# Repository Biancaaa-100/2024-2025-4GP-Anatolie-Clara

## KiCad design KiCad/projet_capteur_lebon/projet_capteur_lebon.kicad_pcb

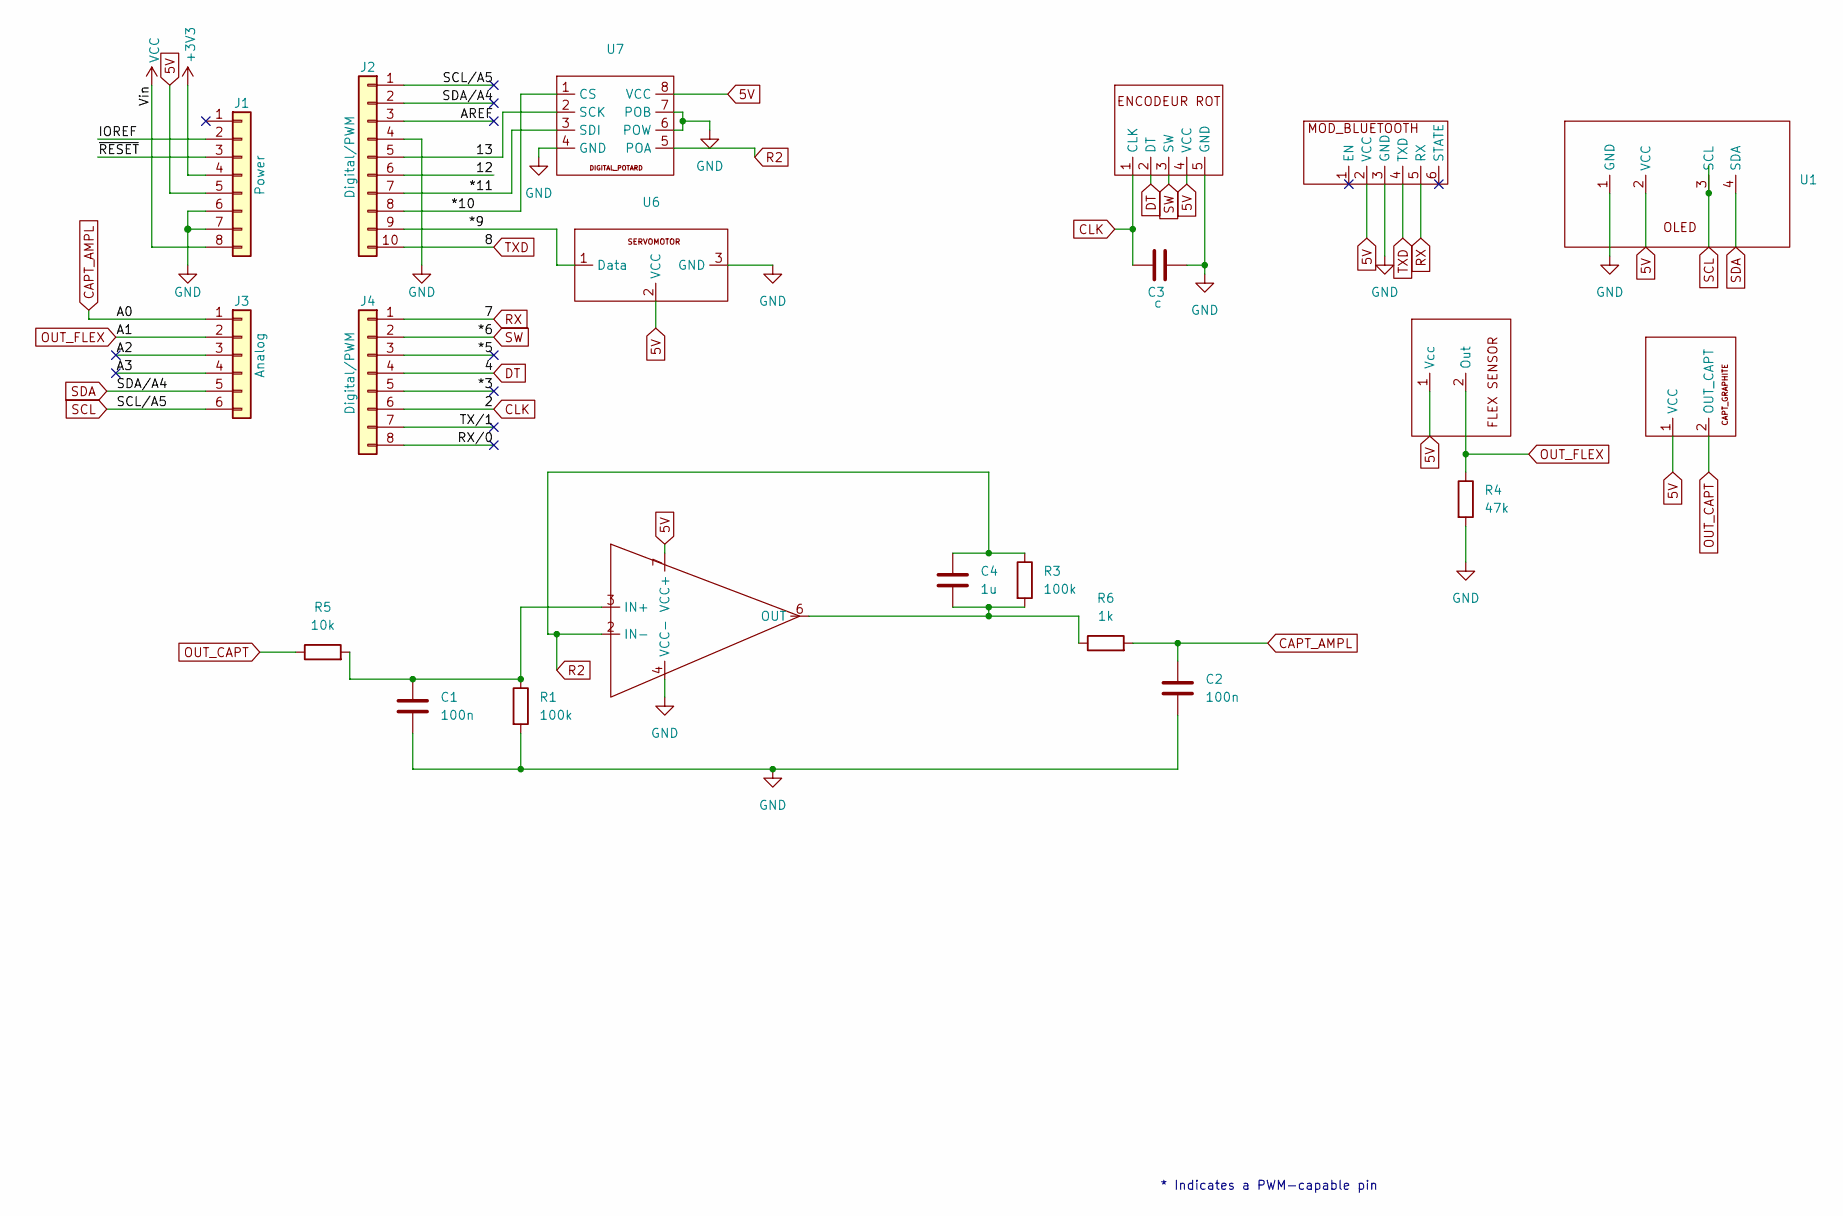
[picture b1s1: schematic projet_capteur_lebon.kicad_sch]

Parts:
C1, C2: 100n; C_Disc_D6.0mm_W2.5mm_P5.00mm
C3: c; C_Disc_D6.0mm_W2.5mm_P5.00mm
C4: 1u; C_Disc_D6.0mm_W2.5mm_P5.00mm
J1: Power; PinSocket_1x08_P2.54mm_Vertical
J2: Digital/PWM; PinSocket_1x10_P2.54mm_Vertical
J3: Analog; PinSocket_1x06_P2.54mm_Vertical
J4: Digital/PWM; PinSocket_1x08_P2.54mm_Vertical
R1, R3: 100k; R_Axial_DIN0207_L6.3mm_D2.5mm_P5.08mm_Vertical
R4: 47k; R_Axial_DIN0207_L6.3mm_D2.5mm_P5.08mm_Vertical
R5: 10k; R_Axial_DIN0207_L6.3mm_D2.5mm_P5.08mm_Vertical
R6: 1k; R_Axial_DIN0207_L6.3mm_D2.5mm_P5.08mm_Vertical
U1: SIP-4
U2: ENCODEUR ROT
U4, U7: DIP-8_296
U5: SIP-2
U6: SIP-3
U8: CAPTEUR_GRAPHITE
U9: BLUETOOTH

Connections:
5V: J1.5, U1.2 (VCC), U2.4 (VCC), U4.7 (VCC+), U5.1 (Vcc), U6.2 (VCC), U7.8 (VCC), U8.1 (VCC), U9.2 (VCC)
+3V3: J1.4
/12: J2.6
/13: J2.5, U7.2 (SCK)
/*3: J4.5
/*5: J4.3
/*9: J2.9, U6.1 (Data)
/*10: J2.8, U7.1 (CS)
/*11: J2.7, U7.3 (SDI)
/A2: J3.3
/A3: J3.4
/AREF: J2.3
/IOREF: J1.2
/RX/0: J4.8
/TX/1: J4.7
/~RESET: J1.3
CAPT_AMPL: C2.1, J3.1, R6.2
CLK: C3.1, J4.6, U2.1 (CLK)
DT: J4.4, U2.2 (DT)
GND: C1.2, C2.2, C3.2, J1.6, J1.7, J2.4, R1.2, R4.2, U1.1 (GND), U2.5 (GND), U4.4 (VCC-), U6.3 (GND), U7.4 (GND), U7.6 (POW), U7.7 (POB), U9.3 (GND)
unnamed: C1.1, R1.1, R5.2, U4.3 (IN+)
unnamed: C4.2, R3.2, R6.1, U4.6 (OUT)
OUT_CAPT: R5.1, U8.2 (OUT_CAPT)
OUT_FLEX: J3.2, R4.1, U5.2 (Out)
R2: C4.1, R3.1, U4.2 (IN-), U7.5 (POA)
RX: J4.1, U9.5 (RX)
SCL: J2.1, J3.6, U1.3 (SCL)
SDA: J2.2, J3.5, U1.4 (SDA)
SW: J4.2, U2.3 (SW)
TXD: J2.10, U9.4 (TXD)
VCC: J1.8

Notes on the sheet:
* Indicates a PWM-capable pin

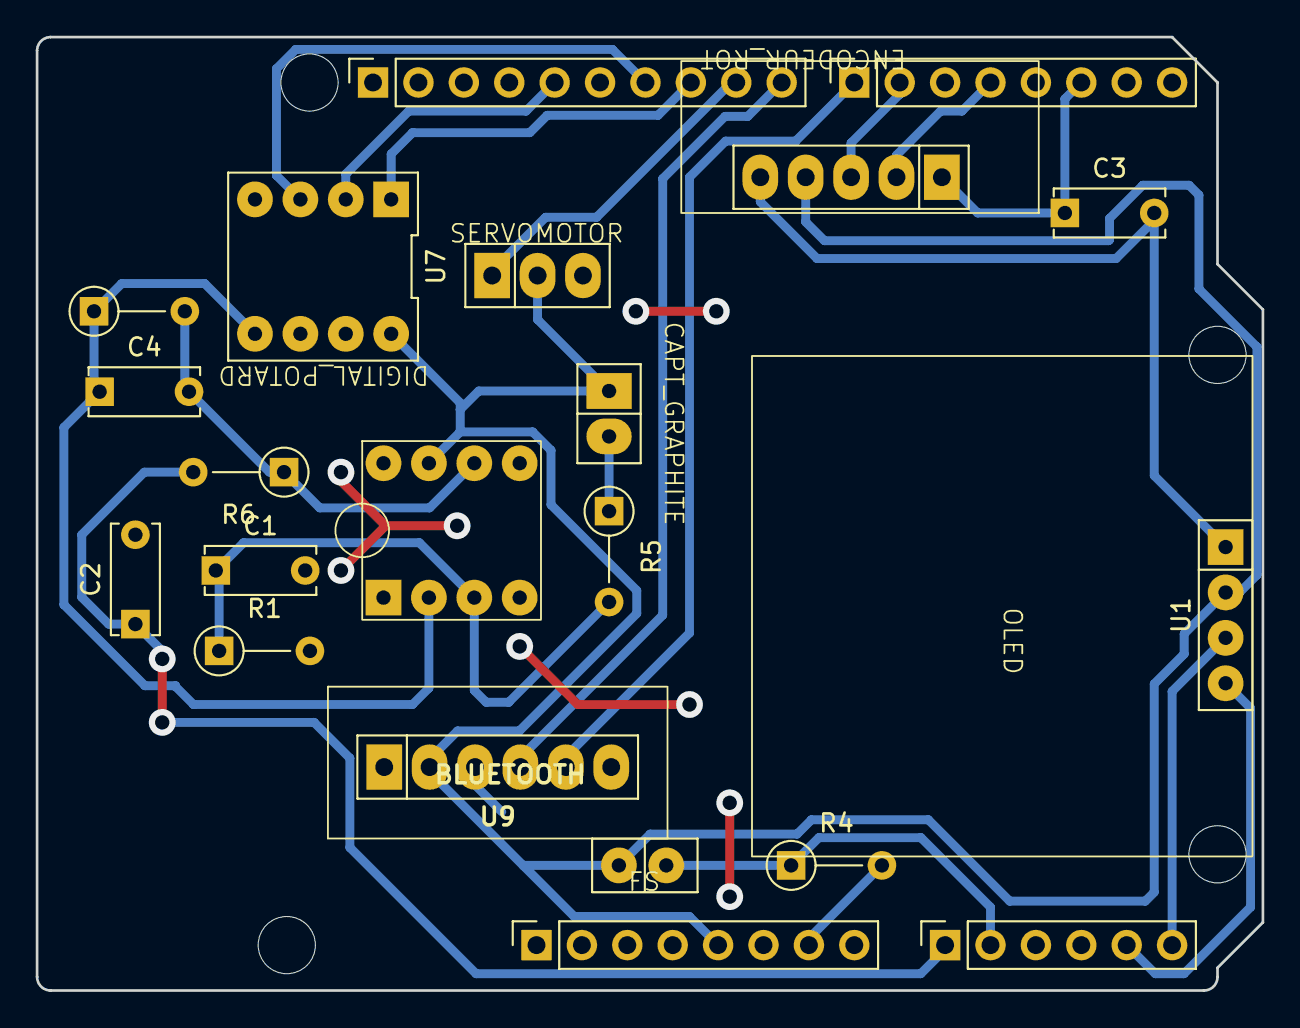
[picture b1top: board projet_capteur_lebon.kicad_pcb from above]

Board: 2 copper layers, 68.6 x 53.3 mm, 25 parts (0 on the bottom side), 19 nets.

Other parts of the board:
MH1, MH2, MH3, MH4: MountingHole_3.2mm

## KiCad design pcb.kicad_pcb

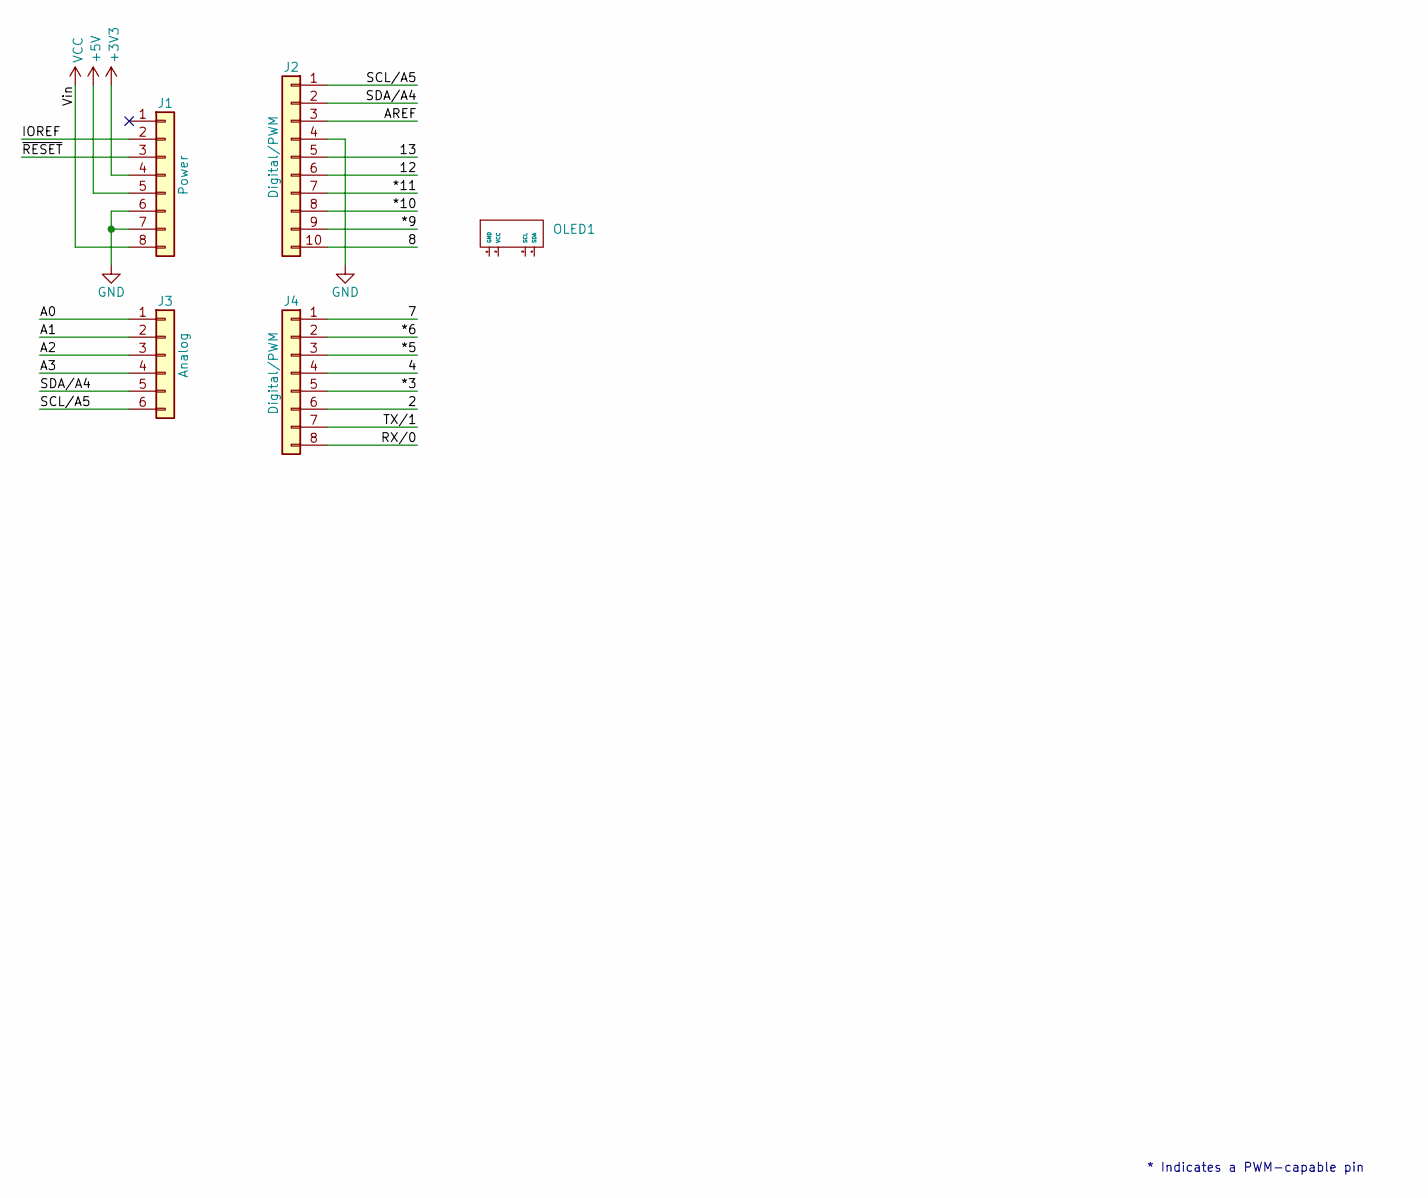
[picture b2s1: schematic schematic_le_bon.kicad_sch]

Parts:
J1: Power; PinSocket_1x08_P2.54mm_Vertical
J2: Digital/PWM; PinSocket_1x10_P2.54mm_Vertical
J3: Analog; PinSocket_1x06_P2.54mm_Vertical
J4: Digital/PWM; PinSocket_1x08_P2.54mm_Vertical
OLED1: SIP-4

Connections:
+3V3: J1.4
+5V: J1.5
/2: J4.6
/4: J4.4
/7: J4.1
/8: J2.10
/12: J2.6
/13: J2.5
/*3: J4.5
/*5: J4.3
/*6: J4.2
/*9: J2.9
/*10: J2.8
/*11: J2.7
/A0: J3.1
/A1: J3.2
/A2: J3.3
/A3: J3.4
/AREF: J2.3
/IOREF: J1.2
/RX/0: J4.8
/SCL/A5: J2.1, J3.6
/SDA/A4: J2.2, J3.5
/TX/1: J4.7
/~RESET: J1.3
GND: J1.6, J1.7, J2.4
VCC: J1.8

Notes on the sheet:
* Indicates a PWM-capable pin

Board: 2 copper layers, 9 parts (0 on the bottom side), 3 nets, no tracks yet.

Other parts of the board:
MH1, MH2, MH3, MH4: MountingHole_3.2mm

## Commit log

2025-03-05 commit initial de la schématique
2025-03-11 dossier kicad
2025-03-11 ajout pcb déjà fait en cours avec juste oled
2025-03-11 pcb dans dossier Kicad
2025-03-11 ajout du schematic correct
2025-03-11 supression ancien shematic
2025-03-12 suppression de tout, on recommence proprement
2025-03-12 maj apres remise a 0
2025-03-12 création fichier txt
2025-03-12 huifhdsgbf
2025-03-12 création fichier
2025-03-12 création fichier pour de vrai
2025-03-12 Création symbole + empreinte OLED
2025-03-12 modele 3D oled
2025-03-12 modèle 3d oled + flex sensor
2025-03-12 modele 3d flex sensor
2025-03-12 mep modele 3d flex s
2025-03-12 modif flex sensor
2025-03-12 ajout modeles 3d
2025-03-12 creation ampli
2025-03-12 travail sur l'ampli transimpedance
2025-03-12 mep bluetooth et fin ampli
2025-03-12 resistance flex
2025-03-12 ajout librairies
2025-03-12 encodeur rot + verifs
2025-03-12 a faire
2025-03-13 capteur graphite symbole et empreintes
2025-03-13 Etiquette
2025-03-13 etiquettes + digital pot
2025-03-13 fin schématique liaisons etc reste debug U5
2025-03-16 modeles 3d et routage
2025-03-17 finitions pcb et gerber
2025-03-17 capa c3 valeur
